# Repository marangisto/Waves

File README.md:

# Waves
Cordic Accelerated Voltage Controlled Oscillator

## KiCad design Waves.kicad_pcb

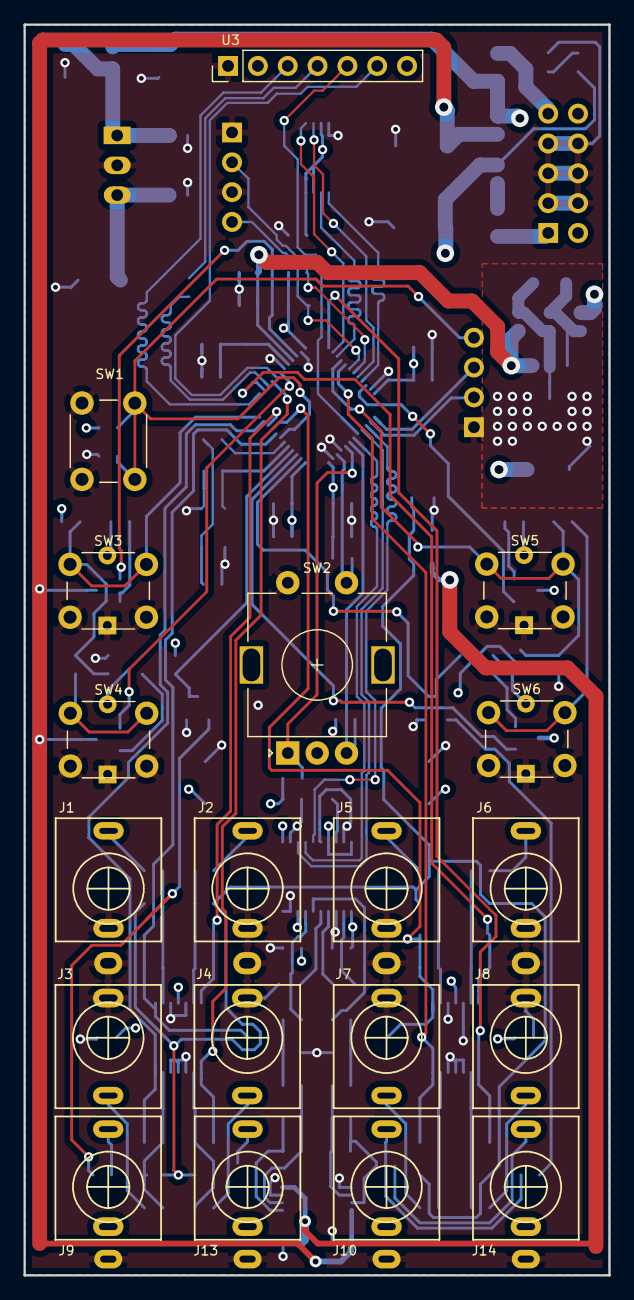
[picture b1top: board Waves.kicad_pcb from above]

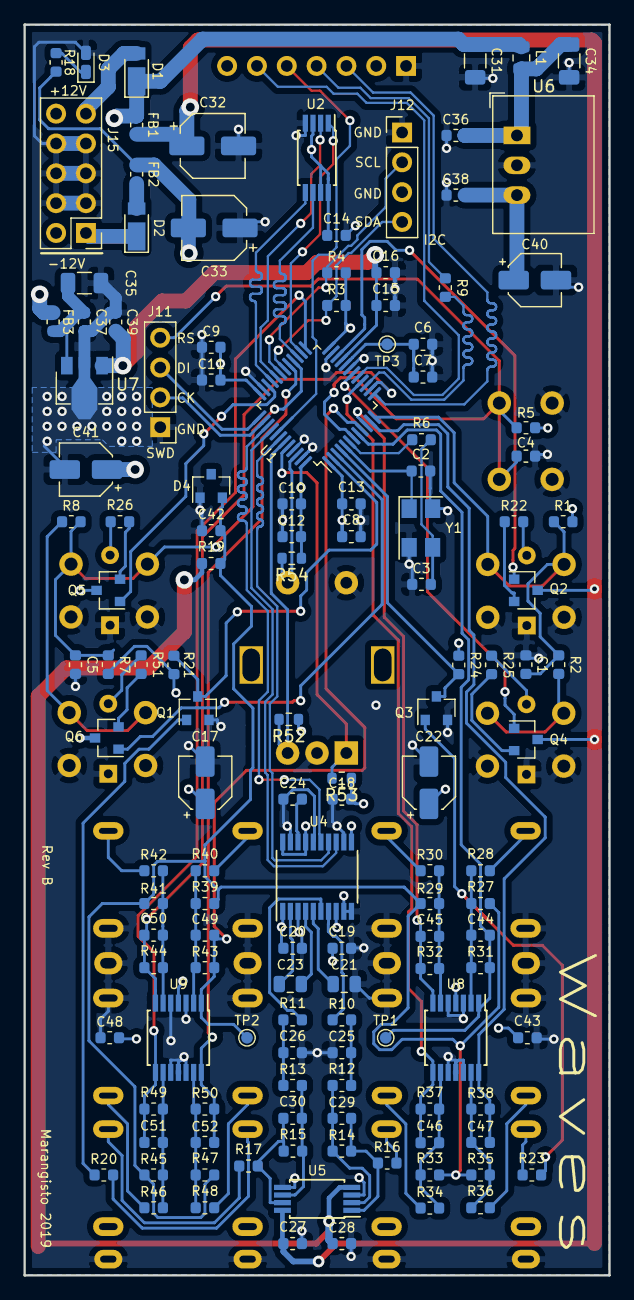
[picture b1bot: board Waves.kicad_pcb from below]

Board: 4 copper layers, 49.8 x 106.5 mm, 154 parts (135 on the bottom side), 97 nets.

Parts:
C1, C4, C5, C6, C11, C12, C13, C14, C18, C19, C20, C24, C27, C28, C36, C37, C38, C39, C43, C48: 100n; C_0603_1608Metric
C2, C3: 27p; C_0603_1608Metric
C7, C8, C9, C10, C16, C42: 1u; C_0603_1608Metric
C15: 10n; C_0603_1608Metric
C17, C22, C40, C41: 10u; CP_Elec_4x5.8
C21, C23: 2u2; C_0805_2012Metric
C25, C26: 2n2; C_0603_1608Metric
C29, C30: 100p; C_0603_1608Metric
C31, C34, C35: 22u; C_1206_3216Metric
C32, C33: 22u; CP_Elec_5x5.4
C44, C45, C46, C47, C49, C50, C51, C52: 470p; C_0603_1608Metric
D1, D2: DFLR1400-7; D_PowerDI-123
D3: LED; LED_0603_1608Metric_Castellated
D4: LM4040DBZ-10; SOT-23
FB1, FB2, FB3: Ferrite_Bead; L_0603_1608Metric
J1, J2, J3, J4, J5, J6, J7, J8, J9, J10, J13, J14: AudioJack2_SwitchT; PJ398SM
J11, J12: Conn_01x04_Male; PinHeader_1x04_P2.54mm_Vertical
J15: Conn_02x05_Odd_Even; PinHeader_2x05_P2.54mm_Vertical
L1: 33u; L_0805_2012Metric
Q1, Q2, Q3, Q4, Q5, Q6: BC847; SOT-23
R1, R2, R3, R4, R7, R8, R52, R53, R54: 4k7; R_0603_1608Metric
R5, R21, R24: 10k; R_0603_1608Metric
R6, R10, R11: 470; R_0603_1608Metric
R9, R16, R17, R18: 1k; R_0603_1608Metric
R12, R13: 18k; R_0603_1608Metric
R14, R15, R31, R43: 33k; R_0603_1608Metric
R19: 2k2; R_0603_1608Metric
R20, R23, R28, R30, R34, R36, R40, R42, R46, R48: 100k; R_0603_1608Metric
R22, R25, R26, R51: 47; R_0603_1608Metric
R27, R39: 169k; R_0603_1608Metric
R29, R33, R35, R41, R45, R47: 200k; R_0603_1608Metric
R32, R37, R38, R44, R49, R50: 56k; R_0603_1608Metric
SW1: SW_Push; SW_PUSH_6mm
SW2: Rotary_Encoder_Switch; RotaryEncoder_Alps_EC11E-Switch_Vertical_H20mm
SW3, SW4, SW5, SW6: SW_Push_LED; SW_PUSH_LED_6mm
TP1, TP2, TP3: TestPoint; TestPoint_Pad_D1.0mm
U1: STM32G431; LQFP-48_7x7mm_P0.5mm
U2: AT25xxx; TSSOP-8_4.4x3mm_P0.65mm
U3: IPS240x240
U4: PCM5100; TSSOP-20_4.4x6.5mm_P0.65mm
U5: TL072; TSSOP-8_4.4x3mm_P0.65mm
U6: R-78E3.3-0.5; Converter_DCDC_RECOM_R-78E-0.5_THT
U7: LD2981ABU33TR; SOT-89-3
U8, U9: MCP6004; TSSOP-14_4.4x5mm_P0.65mm
Y1: 8MHz; Crystal_SMD_5032-4Pin_5.0x3.2mm

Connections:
+3.3VA: C15.1, C16.1, C19.1, C20.1, C22.1, C39.1, C41.1, C43.1, C48.1, J9.TN, J10.TN, U1.21, U4.1, U4.8, U7.1, U8.4, U9.4
+3V3: C8.1, C9.1, C10.1, C11.1, C12.1, C13.1, C14.1, C17.1, C18.1, C38.1, C40.1, R1.1, R3.1, R4.1, R5.1, R7.1, R21.1, R24.1, R52.1, R53.1, R54.1, U1.1, U1.24, U1.36, U1.48, U2.3, U2.7, U2.8, U3.2, U3.7, U4.11, U4.17, U4.20, U6.3
+12V: C27.1, C32.1, FB1.1, Q2.3, Q4.3, Q5.3, Q6.3, U5.8
-12V: C28.2, C33.2, FB2.1, R18.2, R19.1, U5.4
/DAC/OUTL: J13.T, R16.1
/DAC/OUTR: J14.T, R17.1
/QuadCV/CV1: J2.T, R30.2
/QuadCV/CV2: J3.T, R36.2
/QuadCV/CV3: J4.T, R34.2
/QuadCV/VOCT: J1.T, R28.2
/sheet5DE20AC9/In: J10.T, R20.1
/sheet5E1FC1E7/CV1: J6.T, R42.2
/sheet5E1FC1E7/CV2: J7.T, R48.2
/sheet5E1FC1E7/CV3: J8.T, R46.2
/sheet5E1FC1E7/VOCT: J5.T, R40.2
/sheet5E008663/In: J9.T, R23.1
BTN1: C1.1, R1.2, R2.1, SW3.1, U1.12
BTN2: R2.2, SW4.1
BTN3: C5.1, R7.2, R8.1, SW5.1, U1.28
BTN4: R8.2, SW6.1
CV1A: C44.1, R31.1, TP1.1, U1.8, U8.1
CV1B: C49.1, R43.1, TP2.1, U1.9, U9.1
CV2A: C45.1, R32.1, U1.10, U8.7
CV2B: C50.1, R44.1, U1.14, U9.7
CV3A: C47.1, R38.1, U1.11, U8.14
CV3B: C51.1, R49.1, U1.25, U9.8
CV4A: C46.1, R37.1, U1.16, U8.8
CV4B: C52.1, R50.1, U1.29, U9.14
ENC_CH1: R52.2, SW2.B, U1.43
ENC_CH2: R53.2, SW2.A, U1.44
ENC_SW: R54.2, SW2.S1, U1.46
GND: C1.2, C2.2, C3.2, C4.2, C5.2, C6.2, C7.2, C8.2, C9.2, C10.2, C11.2, C12.2, C13.2, C14.2, C15.2, C16.2, C17.2, C18.2, C19.2, C20.2, C21.2, C22.2, C24.2, C25.2, C26.2, C27.2, C28.1, C31.2, C32.2, C33.1, C34.2, C35.2, C36.2, C37.2, C38.2, C39.2, C40.2, C41.2, C42.2, C43.2, C48.2, D3.2, D4.1, J1.TN, J2.TN, J3.S, J3.TN, J4.S, J4.TN, J5.TN, J6.TN, J7.S, J7.TN, J8.S, J8.TN, J9.S, J10.S, J11.1, J12.1, J12.3, J13.S, J14.S, J15.3, J15.4, J15.5, J15.6, J15.7, J15.8, Q1.2, Q3.2, SW1.1, SW2.C, SW2.S2, SW3.2, SW3.4, SW4.2, SW4.4, SW5.2, SW5.4, SW6.2, SW6.4, U1.19, U1.23, U1.35, U1.45, U1.47, U2.4, U3.1, U4.3, U4.9, U4.10, U4.12, U4.16, U4.19, U5.3, U5.5, U6.2, U7.2, U8.3, U8.5, U8.10, U8.11, U8.12, U9.3, U9.5, U9.10, U9.11, U9.12, Y1.2, Y1.4
I2C_SCL: J12.2, R4.2, U1.31
I2C_SDA: J12.4, R3.2, U1.30
I2S+: U1.42, U4.14
I2S-: U1.40, U4.13
I2S_WS: U1.39, U4.15
LED1: Q2.1, U1.22
LED2: Q4.1, U1.18
LED3: Q5.1, U1.34
LED4: Q6.1, U1.3
MEM_CS: U1.26, U2.1
MEM_MISO: U1.32, U2.2
MEM_MOSI: U1.33, U2.5
MEM_SCK: U1.27, U2.6
unnamed: C2.1, U1.5, Y1.1
unnamed: C3.1, R6.2, Y1.3
unnamed: C21.1, U4.5
unnamed: C23.1, U4.2
unnamed: C23.2, U4.4
unnamed: C24.1, U4.18
unnamed: C25.1, R10.1, R12.2
unnamed: C26.1, R11.1, R13.2
unnamed: C29.1, R14.1, R16.2, U5.1
unnamed: C29.2, R12.1, R14.2, U5.2
unnamed: C30.1, R15.1, R17.2, U5.7
unnamed: C30.2, R13.1, R15.2, U5.6
unnamed: C31.1, D1.1, FB1.2, FB3.2, L1.1
unnamed: C34.1, C36.1, L1.2, U6.1
unnamed: C35.1, C37.1, FB3.1, U7.3
unnamed: C44.2, R27.1, R28.1, R31.2, U8.2
unnamed: C45.2, R29.1, R30.1, R32.2, U8.6
unnamed: C46.2, R33.1, R34.1, R37.2, U8.9
unnamed: C47.2, R35.1, R36.1, R38.2, U8.13
unnamed: C49.2, R39.1, R40.1, R43.2, U9.2
unnamed: C50.2, R41.1, R42.1, R44.2, U9.6
unnamed: C51.2, R45.1, R46.1, R49.2, U9.9
unnamed: C52.2, R47.1, R48.1, R50.2, U9.13
unnamed: D1.2, J15.9, J15.10
unnamed: D2.1, J15.1, J15.2
unnamed: D2.2, FB2.2
unnamed: D3.1, R18.1
unnamed: Q1.1, R20.2
unnamed: Q2.2, R22.2
unnamed: Q3.1, R23.2
unnamed: Q4.2, R25.2
unnamed: Q5.2, R26.2
unnamed: Q6.2, R51.2
unnamed: R6.1, U1.6
unnamed: R9.1, U3.4
unnamed: R10.2, U4.7
unnamed: R11.2, U4.6
unnamed: R22.1, SW3.3
unnamed: R25.1, SW4.3
unnamed: R26.1, SW5.3
unnamed: R51.1, SW6.3
RESET: C4.1, J11.4, R5.2, SW1.2, U1.7
SWCLK: J11.2, U1.38
SWDIO: J11.3, U1.37
TFT+: R9.2, U1.15
TFT-: U1.13, U3.3
TFT_DC: U1.17, U3.6
TFT_RES: U1.41, U3.5
TRIGA: Q3.3, R24.2, U1.4
TRIGB: Q1.3, R21.2, U1.2
VREF: C6.1, C7.1, TP3.1, U1.20
VRef-10: C42.1, D4.2, R19.2, R27.2, R29.2, R33.2, R35.2, R39.2, R41.2, R45.2, R47.2

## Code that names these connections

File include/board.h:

#pragma once

#include <timer.h>
#include <pulse.h>
#include <button.h>
#include <adc.h>
#include <i2s.h>
#include <at25.h>
#include <st7789.h>
#include <text.h>
#include <fifo.h>
#include <message.h>
#include "dacdma.h"
#include "types.h"

namespace board
{

using namespace dacdma;

typedef tim_t<7> aux_tim;

// CV inputs
/*
typedef analog_t<PA0> cv1a;
typedef analog_t<PA2> cv2a;
typedef analog_t<PA3> cv3a;
typedef analog_t<PB0> cv4a;
typedef analog_t<PA1> cv1b;
typedef analog_t<PA6> cv2b;
typedef analog_t<PB11> cv3b;
typedef analog_t<PB15> cv4b;
*/

// trigger inputs
typedef input_t<PC13> trigb;
typedef input_t<PC15> triga;

// user controls
typedef encoder_t<4, PB6, PB7> encoder;
typedef button_t<PB9> encoder_btn;
//typedef analog_t<PA4> btnsa;
//typedef analog_t<PB14> btnsb;
typedef pulse_t<PB10> led1;
typedef pulse_t<PB2> led2;
typedef pulse_t<PA12> led3;
typedef pulse_t<PC14> led4;

// peripherals

typedef at25_t<256, spi_t<2, PB13, PA11, PA10>, PB12> eeprom;
typedef st7789_t<1, PA5, PA7, PB1, PB4> tft;
typedef text::console_t<tft> console;
typedef i2s_t<3, PB3, PB5, PA15> dac;
typedef dacdma_t<dac, 2, 1, 128> dacdma;
typedef output_t<PA10> mem_miso;
typedef output_t<PA11> mem_mosi;
typedef output_t<PA8> i2c_sda;
typedef output_t<PA9> i2c_scl;
typedef output_t<PB12> mem_cs;
typedef output_t<PB13> mem_sck;

// event message queue
typedef fifo_t<message_t, 0, 8> mq;

typedef tim_t<3> adc_tim;
typedef adc_t<1> adc1;
typedef adc_t<2> adc2;
typedef dma_t<1> adc_dma;
static const uint8_t adc1_dma_ch = 1;
static const uint8_t adc2_dma_ch = 2;
static const uint32_t adc_sample_freq = 4000;
static const uint8_t adc_buf_size = 7;
extern uint16_t adc1_buf[adc_buf_size];
extern uint16_t adc2_buf[adc_buf_size];

template<uint8_t CH> inline uint16_t reada();
template<uint8_t CH> inline uint16_t readb();

template<> inline uint16_t reada<0>() { return adc1_buf[1]; }
template<> inline uint16_t reada<1>() { return adc1_buf[3]; }
template<> inline uint16_t reada<2>() { return adc1_buf[4]; }
template<> inline uint16_t reada<3>() { return adc1_buf[5]; }
template<> inline uint16_t reada<4>() { return adc2_buf[6]; }

template<> inline uint16_t readb<0>() { return adc2_buf[1]; }
template<> inline uint16_t readb<1>() { return adc2_buf[3]; }
template<> inline uint16_t readb<2>() { return adc2_buf[4]; }
template<> inline uint16_t readb<3>() { return adc2_buf[5]; }
template<> inline uint16_t readb<4>() { return adc1_buf[6]; }

void read_cv_a(ctrl_t& ctrl);

void read_cv_b(ctrl_t& ctrl);

void setup();

void start_io();

void start_dacdma();

} // namespace board

void manual_trigger(ch_t ch, bool gate);
void register_triggers(itrigger *a, itrigger *b);

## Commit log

2019-08-24 Board abstraction with message queue.
2019-08-24 Eliminate encoder double-stepping.
2019-08-24 Added analog to digital conversion setup.
2019-08-25 Added output stage and signal generators.
2019-08-25 Stiched in cordic signal generator.
2019-08-25 Basic FM.
2019-08-25 Added rational ratios and cv-pot for index.
2019-08-27 Added stm32g431 symbol.
2019-09-01 Through-zero FMmk upload
2019-09-01 Variable index depth.
2019-09-03 More rationals.
2019-09-03 Added external cv volt / octave input.
2019-09-05 First reasonable cv tracking.
2019-10-19 Assigned some footprints.
2019-10-19 Moved DAC to separate sheet.
2019-10-19 Added power.
2019-10-19 Decoupling caps and voltage reference.
2019-10-20 Major pin-assignments and some IO hardware.
2019-10-20 Assigned ADC inputs and I2C expansion bus.
2019-10-20 Triggers and buttons.
2019-10-20 CV inputs, including spice checks.
2019-10-20 Split analog ground and DRC checks.
2019-10-20 Renamed project to Waves.
2019-10-20 Layout and edgecuts.
2019-10-20 Corrected footprints.
2019-10-21 Drawing adjustments.
2019-10-21 Added a first rendering of the front panel.
2019-10-21 Placed front-side components.
2019-10-21 Corrected power supply for MCP6004.
2019-10-21 Re-annotated.
2019-10-21 Re-annotated schema.
2019-10-21 No split ground.
2019-10-21 First pass of component placement.
2019-10-22 Added fourth led-button and movde reset switch.
2019-10-22 Placed ADC input stages.
2019-10-22 Placed DAC and output stage.
2019-10-22 Added renderings.
2019-10-23 Changed regulators and laid out power components.
2019-10-23 Added another rendering.
2019-10-24 First pass complete layout.
2019-10-24 Ground plane and keep-out for jacks.
2019-10-24 Heat-sink for analog supply.
2019-10-24 Pre-routing state.
2019-10-24 Improved placement and avoidance of criss-crossing.
2019-10-25 Power layer adjustments.
2019-10-25 Via stitch on headsink.
2019-10-25 Swap IC2 and SWD headers.
2019-10-26 Swapped led and trigger pins for better routing.
2019-10-26 More pin swapping and some power routing.
2019-10-26 Routed and length matched all SPI & I2S lines.
2019-10-26 More power routing.
2019-10-26 Routed I2C and analog power.
2019-10-26 Fully routed, clean DRC.
2019-10-26 Merged pads for jacks.
2019-10-26 Front silkscreen.
2019-10-26 Rear silkscreen.
2019-10-26 Rear ground pour.
2019-10-26 Front and power ground pour.
2019-10-26 Length match interfaces.
2019-10-26 No silk-screen on heat-simk.
2019-10-26 Labels and branding
2019-10-26 More clerance on some mcu traces
2019-10-28 Added some more renderings.
2019-10-28 Generated Gerbers.
2019-10-28 Added Gerbers.
2019-10-31 Added BOM.
2019-11-02 Added final panel rendering.
2019-11-10 Define actual board pinout.
2019-11-12 Board running with blinking leds 1-4.
2019-11-13 Added test gui skeleton and enabled tft..
2019-11-14 Some more debug output widgets.
2019-11-16 Polling read of button adc channels.
2019-11-16 Channels a scanned and buffered.
2019-11-16 Second ADC running in DMA mode.
2019-11-17 4kHz sampling frequency with 32x oversampling.
2019-11-17 Swapped channels on adc2 to correct for board layout.
2019-11-17 Working DAC!
2019-11-23 Work on dac over i2s with dma.
2019-11-23 I2S dac with dma working!
2019-11-23 Use HSE for better frequency stability.
2019-11-25 Use exti interrupts for triggers a & b.
2019-11-26 Separated channel fills with dma interrupts.
2019-11-26 Attempting to get cordic signal generator integrated.
2019-11-26 First pair of independent sines generated.
2019-11-28 Initial envelope implementation.
2019-11-29 Continuity on re-triggers.
2019-11-30 Exponential envelope response.
2019-11-30 Run both channels.
2019-11-30 Adjusted sampling frequency to match clock and added CV/oct.
2019-11-30 Set frequency inside I2S interrupt handler for more frequent update.
2019-11-30 Added sheet for some calculations.
2019-12-02 Process encoder and buttons.
2019-12-02 Debounce the button inputs.
2019-12-03 Removed obsolete output header.
2019-12-03 Added dac dma load measurement.
2019-12-10 Swapped channels for correct order to DAC.
2019-12-11 Corrected encoder direction.
2019-12-16 Use function template for signal generators in dacdma.
2019-12-16 Revived classic waveforms.
2019-12-17 Partial change to use fix point arithmetic in phase accumulator.
2019-12-17 Phase accumulator and primitive signals all in q31 format.
2019-12-18 Rewrote exponential response in fixed point.
2019-12-18 Fixed point arithmetic for envelope.
2019-12-19 Combine signal generator and envelope into operator.
2019-12-19 Two-operator FM!
2019-12-24 Added gui emulator.
2019-12-25 Show notes and cents.
2019-12-25 Refactored message handling code for reuse in emulator.
2019-12-25 Added program selection.
2019-12-25 Attempt at sub-program interface.
2019-12-25 List-based focus.
2019-12-25 Ability to navigate in and out of sub-program gui.
2019-12-25 Integrated new gui into firmware.
2019-12-25 Use quiet property update when showing program ui.
2019-12-25 Initialize gui before operators.
2019-12-25 Place note widget in top row.
2019-12-25 Cleaned up obsolete code.
2019-12-26 Added load indicator.
2019-12-26 Minor color adjustments.
2019-12-26 Bound user interface to operators.
2019-12-27 Added tuning, transpose and scale controls.
2019-12-27 Added navigation for new fields.
2019-12-27 Preliminary integration of volt-per-octave core.
2019-12-27 Added board test program.
2019-12-27 Use chromatic scale on boot.
2019-12-28 Introduced model interface.
2019-12-28 Improved member variable naming.
2019-12-28 Better sharing of control voltage code.
2019-12-28 Eliminated model pointer.
2019-12-28 Basic scales (no modes or variations).
2019-12-28 Added ability to open envelope (0, 0) setting.
2019-12-28 Added classic waveform model.
2019-12-28 Resimplified signal generator.
2019-12-29 Bound waveforms in classic model.
2019-12-29 Added type header.
2019-12-29 Added mixing weight and detuning to classic model.
2019-12-29 Alternate color for freqmod labels.
2019-12-30 Use screen_t from widget to reduce duplicated code.
2019-12-30 Preliminary FM index matrix support.
2019-12-30 Added kick-drum model.
2019-12-30 Added basic snare drum.
2019-12-31 Added simple hi-hat model.
2020-07-30 Partial port to new widget library.
2020-07-30 Better initial settings and 0V at midi note 57.
2020-07-30 Skeleton calibration model.
2020-08-01 Completed calibration sampling logic.
2020-08-01 Working calibration.
2020-08-01 Window framing and positioning.
2020-08-01 Sombre theme.
2020-08-23 Created firmware directory.
2020-08-23 Bring up TFT on corona.
2020-08-23 Use corona for build.
2020-08-23 Ported to corona.
2020-08-23 Detect both edges and call model with gate.
2020-08-23 Added ADSR support to FM model.
2020-08-23 Better initial settings.
2020-10-21 Use new HSE definition.
2020-10-22 Added basic dump test for on-board at25.
2020-10-23 Extended calibration strategy.
2020-10-25 Properly working console.
2020-10-25 Use corona hexdump.
2020-10-25 Reorganized files for better sharing.
2020-10-25 Use message queue for demo apps.
2020-10-25 Skeleton AutoTune.
2020-10-26 Refactored trigger with call-backs.
2020-10-26 Refactored analog input code.
2020-10-27 Compute bucketed averages.
2020-10-27 Removed obsolete file.
2020-10-28 Bucket results and calibration compare.
2020-10-30 Reusable menu code.
2020-10-30 Load and save of tuning data.
2020-10-30 Refactored trigger callback code.
2020-10-30 Separate compile board initialization and statics.
2020-11-01 Refactored to enable better reuse.
2020-11-01 Launch auto-tune when encoder pressed on reset.
2020-11-02 Added tuning interpolator.
2020-11-02 Removed old calibration code.
2020-11-02 Load tuning and use it.
2020-11-02 Fixed adc to cv translation.
2020-11-04 Initial Karplus-Strong implementation.
2020-11-04 Added tool to generate Gaussian kernels.
2020-11-04 Generate full-fledged code.
2020-11-04 Generated Gaussian kernels.
2020-11-05 Use Gaussian kernels and shifting for accurate tuning.
2020-11-06 Use Epanechnikov based kernel.
2020-11-07 Rename kernels.
2020-11-07 Renamed kernel.
2020-11-07 Turned model into reusable component.
2020-11-07 Rescale period to fit smaller delay line.
2020-11-12 Minor optimizations.
2020-11-12 Refactored plucked string logic.
2020-11-12 Pitch control in interface.
2020-11-21 Added modulation interface.
2020-11-21 Added mod for kernel width.
2020-11-21 Moved exponential approximation to fixed header.
2020-11-21 Use exponential response.
2020-11-21 Added stride to generator interface.
2020-11-21 Better defaults.
2020-11-21 Use new generator interace for FM synth.
2020-11-21 First working KS model on Waves hardware.
2020-11-22 Ad-hock frequency dependent mods.
2020-11-28 Use numeric header.
2020-11-28 Use floats remapped to [0,1] for mod cv inputs.
2020-11-28 Renumbred buttons from 1 to allow release encoding.
2020-11-28 Added manual triggers (with gate).
2020-11-28 Use chromatic quantization for less noise with Karplus-Strong.
2020-11-28 Added gate decay (cv-mod not working).
2020-11-29 Fixed decay modulation bug.
2020-11-29 Wider kernel higher up.
2020-12-03 Added pull-ups on encoder.
